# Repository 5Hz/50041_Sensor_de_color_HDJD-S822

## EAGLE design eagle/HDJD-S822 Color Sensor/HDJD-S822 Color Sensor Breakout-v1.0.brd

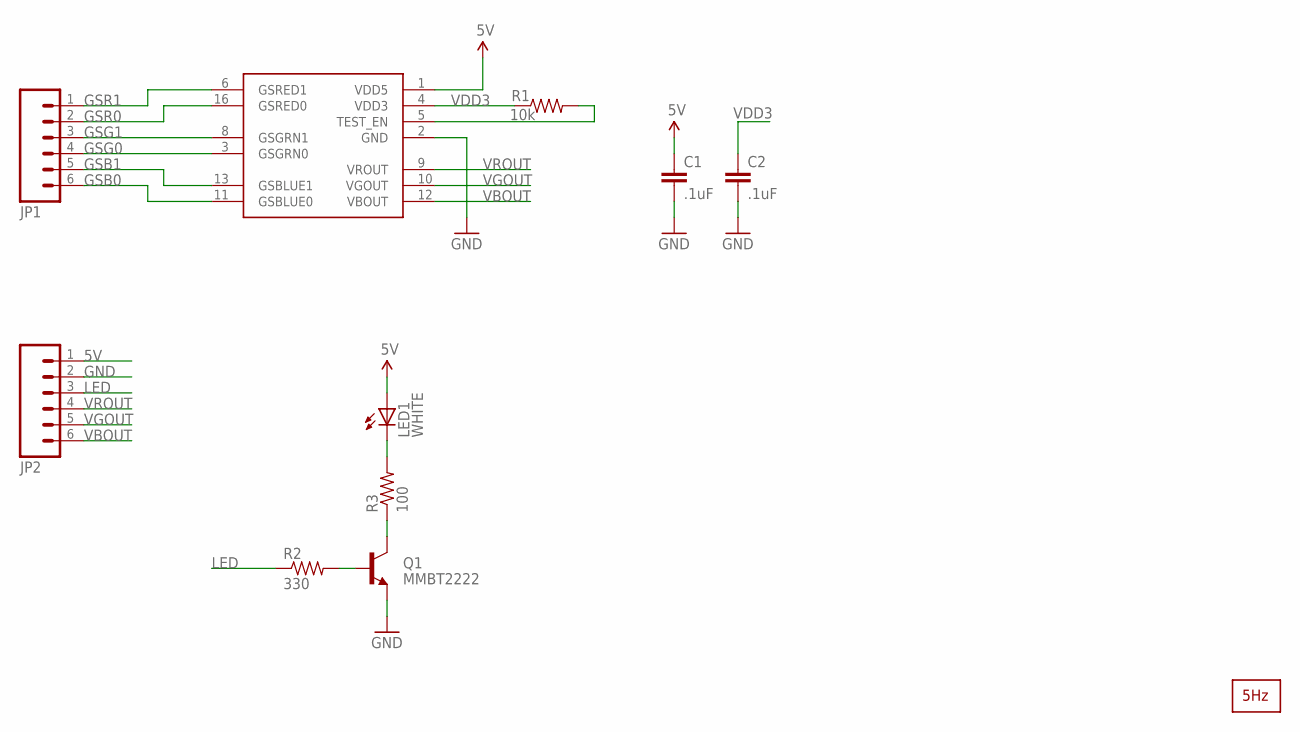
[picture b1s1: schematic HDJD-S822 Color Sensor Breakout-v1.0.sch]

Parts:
C1, C2: .1uF; 0402-CAP
JP1, JP2: M06SIP; 1X06
LED1: WHITE; LED-0603
Q1: MMBT2222; SOT23-3
R1: 10k; 0402-RES
R2: 330; 0402-RES
R3: 100; 0402-RES
U$1: HDJD-S822-QR999ROUNDEDTHERMALPAD; QFN-16-(ROUNDED0THERMAL-PAD)
U$2: LOGO2_SILKL5MM; LARGO2_5MM

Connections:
5V: C1.1, JP2.1, LED1.A, U$1.1 (VDD5)
GND: C1.2, C2.2, JP2.2, Q1.2 (E), U$1.2 (GND)
GSB0: JP1.6, U$1.11 (GSBLUE0)
GSB1: JP1.5, U$1.13 (GSBLUE1)
GSG0: JP1.4, U$1.3 (GSGRN0)
GSG1: JP1.3, U$1.8 (GSGRN1)
GSR0: JP1.2, U$1.16 (GSRED0)
GSR1: JP1.1, U$1.6 (GSRED1)
LED: JP2.3, R2.1
unnamed: LED1.C, R3.2
unnamed: R1.2, U$1.5 (TEST_EN)
unnamed: Q1.3 (C), R3.1
unnamed: Q1.1 (B), R2.2
VBOUT: JP2.6, U$1.12 (VBOUT)
VDD3: C2.1, R1.1, U$1.4 (VDD3)
VGOUT: JP2.5, U$1.10 (VGOUT)
VROUT: JP2.4, U$1.9 (VROUT)

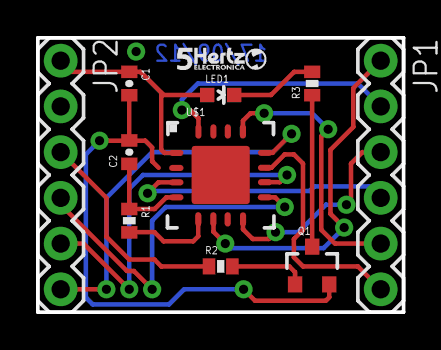
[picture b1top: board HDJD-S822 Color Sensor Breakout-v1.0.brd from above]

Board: 2 copper layers, 20.3 x 15.2 mm, 11 parts (0 on the bottom side), 17 nets.

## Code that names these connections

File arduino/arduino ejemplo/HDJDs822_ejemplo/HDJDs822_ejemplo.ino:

/************************************************************************
** Código creado en Electrónica 5Hz                                    **
** www.5hz-electronica.com                                             **
** Por:                                                                **
**                                                                     **
** Descripción del código:                                             **
**                                                                     **
** Ejemplo para el sensor de color HDJD-S822                           **
** Coloca un objeto enfrente del sensor y checa en el                  **
** monitor serial los valores que esté leyendo el sensor               **
*************************************************************************
Conexiones:
UNO   HDJD-S822

5V    5V
GND   GND
3     LED
A0    VR
A1    VG
A2    VB

Conecta los pines de ganancia del sensor a los pines digitales
7-12 (o a GND)
*/

//--------------------------------------------------definiciones de pines

const int ledpin = 3;
const int GSR1 = 12;
const int GSR0 = 11;
const int GSG1 = 10;
const int GSG0 = 9;
const int GSB1 = 8;
const int GSB0 = 7;

int redpin = A0;
int greenpin = A1;
int bluepin = A2;

int red = 0;
int green = 0;
int blue = 0;

//----------------------------------------------------------configuracion

void setup() 
{
  Serial.begin(9600);

  pinMode(ledpin, OUTPUT);
  pinMode(GSR1, OUTPUT);
  pinMode(GSR0, OUTPUT);
  pinMode(GSG1, OUTPUT);
  pinMode(GSG0, OUTPUT);
  pinMode(GSB1, OUTPUT);
  pinMode(GSB0, OUTPUT);
  analogWrite(ledpin, 100);
  //ajusta las ganancias
  digitalWrite(GSR1, LOW);
  digitalWrite(GSR0, LOW);
  digitalWrite(GSG1, LOW);
  digitalWrite(GSG0, LOW);
  digitalWrite(GSB1, LOW);
  digitalWrite(GSB0, LOW);
  Serial.println("-------------------5HZ ELECTRONICA---------------------------");
  Serial.println("");
  Serial.println("                     PRESENTA");
  Serial.println("");
  Serial.println("*************************************************************");
  Serial.println("");
  Serial.println("      BIEVENIDO AL PROGRAMA DE PRUEBAS DEL HDJD-S822");
  Serial.println("");
  Serial.println("*************************************************************");
  Serial.println("");
}

//########################################################ciclo principal

void loop() 
{
  
  // Lee sensores
  // En la página 7 de la hoja de datos, hay una gráfica de la 
  // respuesta espectral del chip. Los factores de escala fueron
  // seleccionados basados en esta gráfica para que la ganancia de  
  // cada color sea casi igual
  red = analogRead(redpin) * 10;
  green = analogRead(greenpin) * 14;
  blue = analogRead(bluepin) * 17;
  
  //imprime los valores en el monitor serial
  Serial.print("Red: ");
  Serial.print(red, DEC);
  Serial.print("\t\tGreen: ");
  Serial.print(green, DEC);
  Serial.print("\tBlue: ");
  Serial.println(blue, DEC);
  delay(200);
}

//################################################fin del ciclo principal

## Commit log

2014-01-10 creación
